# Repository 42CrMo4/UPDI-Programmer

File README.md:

# UPDI Programmer

Programmer for Attiny UPDI Interface.

ToDos:
* Pogo Pins
    * Design Footprint
* USB-C
    * to Host
    * to Device
* Kabel
    * Pinheader
    * Clamp

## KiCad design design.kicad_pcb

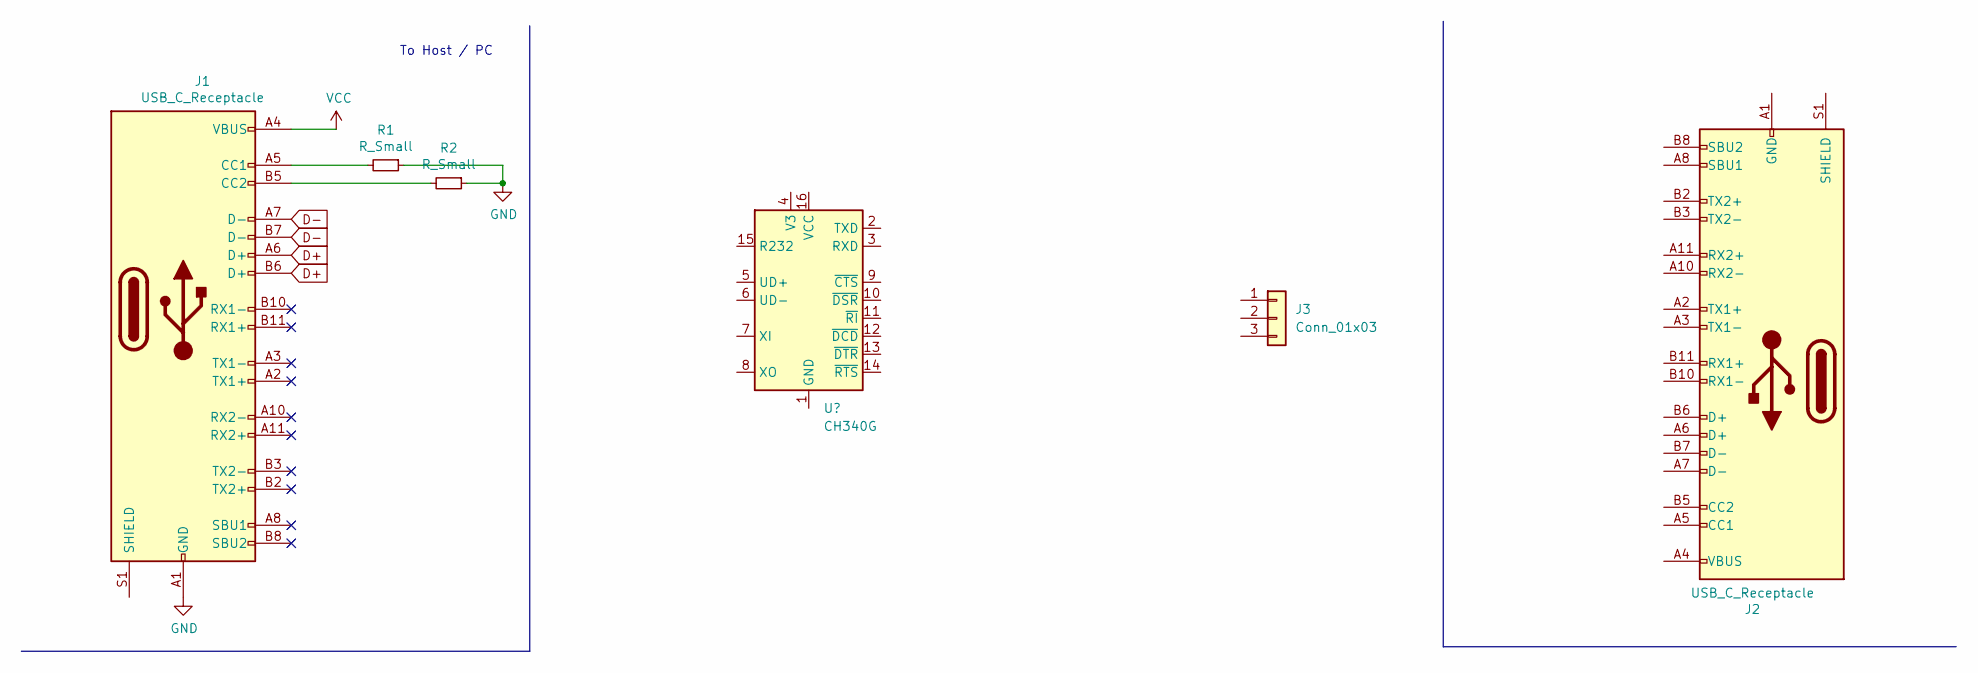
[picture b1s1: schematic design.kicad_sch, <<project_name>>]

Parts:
J1, J2: USB_C_Receptacle; USB_C_Receptacle_HRO_TYPE-C-31-M-12
J3: Conn_01x03; Pogo-Pin-01x03_2.54
R1, R2: R_Small; R_0805_2012Metric

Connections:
D+: J1.A6 (D+), J1.B6 (D+)
D-: J1.A7 (D-), J1.B7 (D-)
GND: J1.A1 (GND), J1.A12 (GND), J1.B1 (GND), J1.B12 (GND), R1.1, R2.1
unnamed: J1.A5 (CC1), R1.2
unnamed: J1.B5 (CC2), R2.2
unnamed: J2.A1 (GND), J2.A12 (GND), J2.B1 (GND), J2.B12 (GND)
unnamed: J2.A4 (VBUS), J2.A9 (VBUS), J2.B4 (VBUS), J2.B9 (VBUS)
VCC: J1.A4 (VBUS), J1.A9 (VBUS), J1.B4 (VBUS), J1.B9 (VBUS)

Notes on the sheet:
To Host / PC

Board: 2 copper layers, 5 parts (0 on the bottom side), 8 nets, no tracks yet.

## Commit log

2021-12-26 init
2021-12-26 Add ToDo
2021-12-29 Add USB C
    KiCad 6 afterwards
2021-12-29 add KiCad 6 backup path to gitignore
2021-12-29 convert to KiCad 6
2022-01-03 bullseye container KiCAD6
2022-01-03 update file extension to kicad6
2022-01-03 bullseye also for pcb workflow
2022-01-03 use dev container
2022-01-03 nightly container
2022-01-03 del: old sch & pro file
    old files from KiCad 5
2022-01-03 change more file extension to kicad_sch
2022-01-03 pcb workflow with nightly container
2022-01-03 more kicad_sch
2022-01-11 use kicad_auto with kibot master
2022-01-17 WF use dev_ki6
2022-01-17 WF Tipo
2022-01-17 WF changed back to setsoft container
2022-01-17 Update Bom
2022-01-20 add qr support
